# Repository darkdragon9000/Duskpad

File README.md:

## Duskpad
Duskpad is a 16-key quad-layer macro pad with an OLED display and underglow RGB using WS2812B leds running QMK and Via. it was built for Hackclub Stardance with the Hackpad misson.

## Features:
- 128x32 OLED Display
- 20 WS2812B RGB LEDs. 16 for per key lighting, and 4 layer indicators
- 16 Keys
- VIA support
  
## CAD Model:
Everything fits together using 6 M3 Bolts and heatset inserts.
It has 3 separate printed pieces. The base, the middle to clamp down on the PCB, and the top cover.

Made in onshape
## PCB
Here's my PCB! It was made in KiCad.

Schematic

## Firmware Overview
This hackpad uses [QMK](https://qmk.fm/) firmware for everything. 

- The 16 keys currently act as macros I dynamically change in VIA.
- 4 preset layers(setting,numpad, and idk what to do with the other 2)
- the top-left key runs a custom key code where, if you tap it, it sends the assigned code for that layer but if you hold it, it'll cycle to the next layer up

## BOM:
Here should be everything you need to make this hackpad

- 16x Cherry MX Switches
- 16x DSA Keycaps
- 6x M3x5x4 Heatset inserts
- 6x M3x16mm SHCS Bolts
- 16x 1N4148 DO-35 Diodes.
- 20x WS2812B LEDs
- 1x 0.91" 128x32 OLED Display
- 1x XIAO RP2040
- 1x Case (3 printed parts)

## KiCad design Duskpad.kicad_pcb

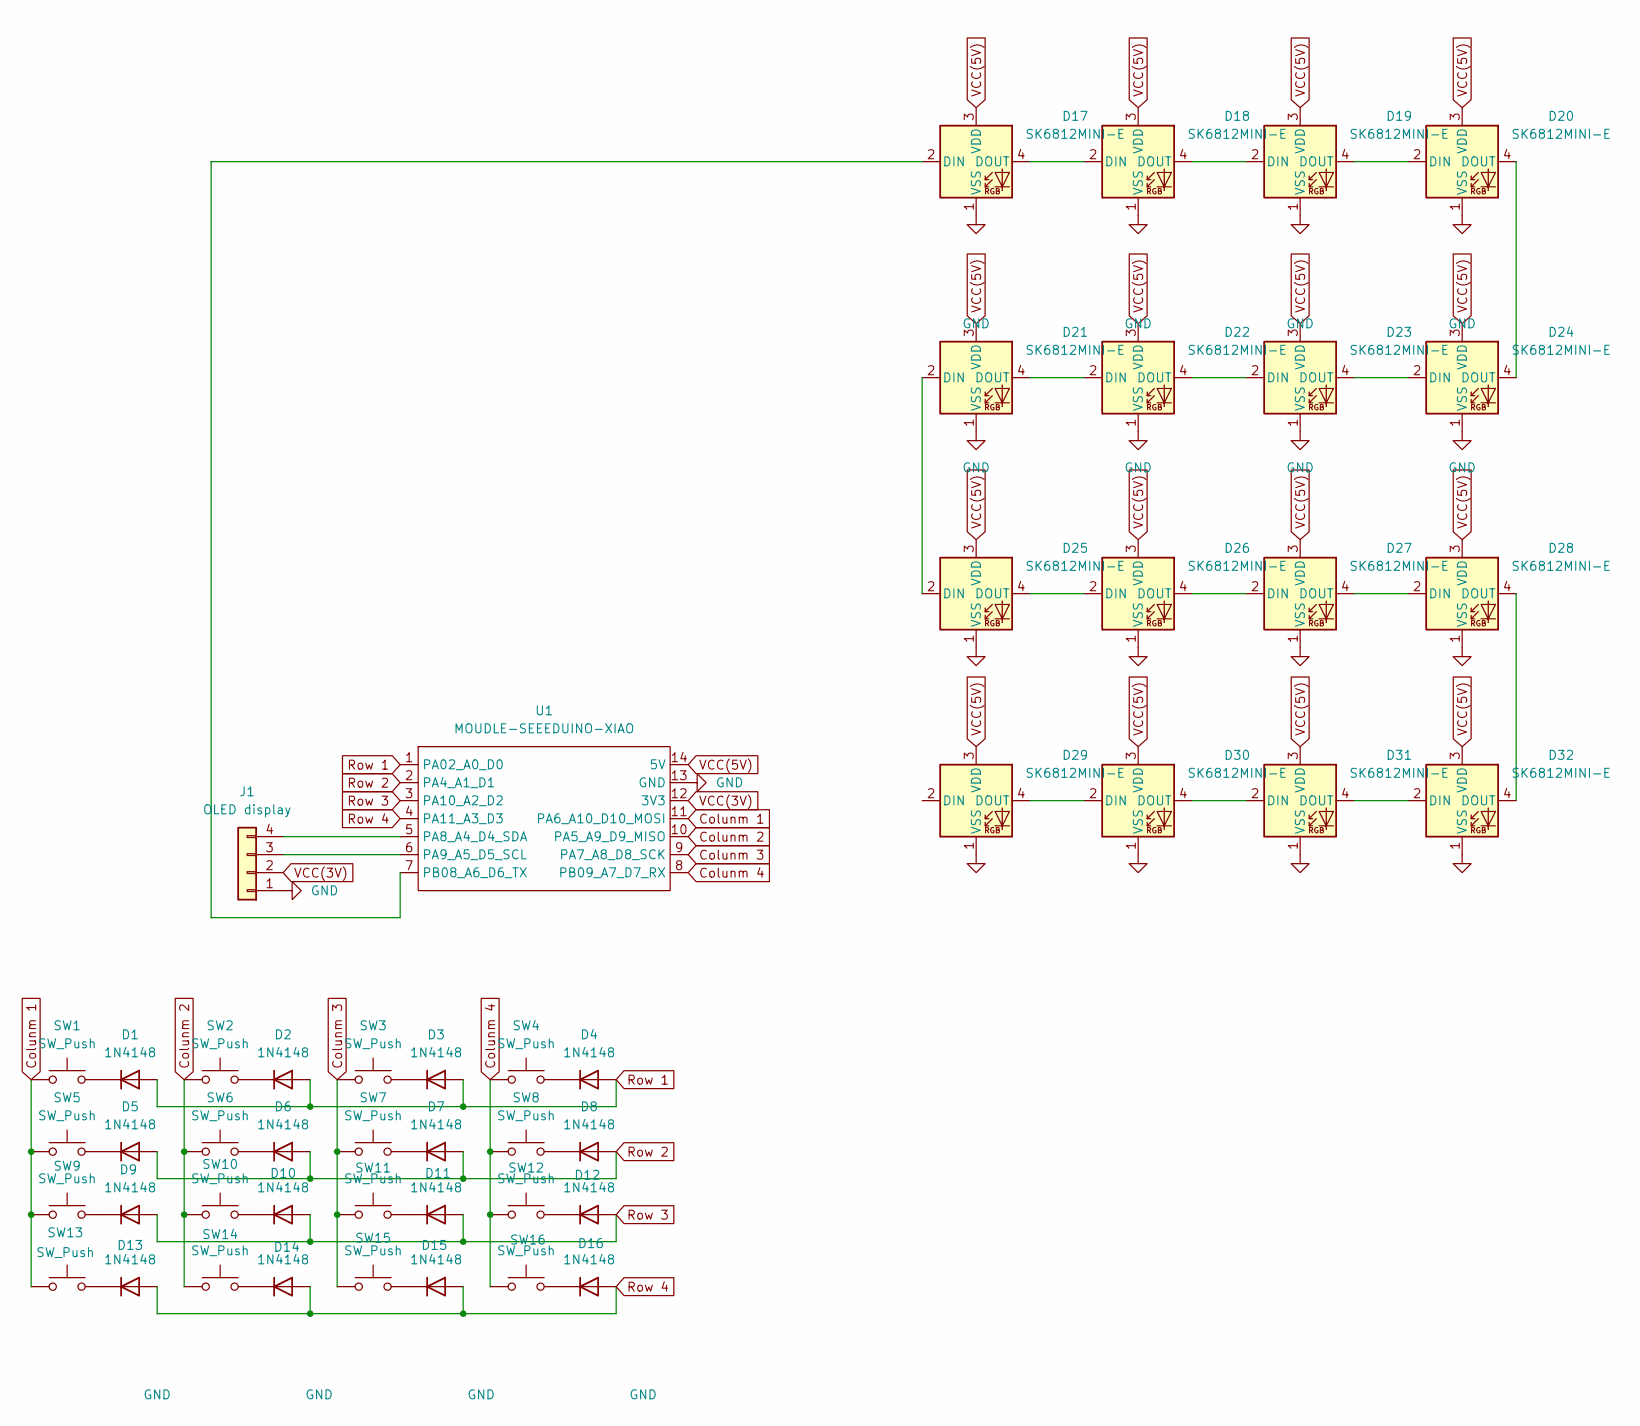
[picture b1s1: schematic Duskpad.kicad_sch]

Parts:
D1, D2, D3, D4, D5, D6, D7, D8, D9, D10, D11, D12, D13, D14, D15, D16: 1N4148; D_DO-35_SOD27_P7.62mm_Horizontal
D17, D18, D19, D20, D21, D22, D23, D24, D25, D26, D27, D28, D29, D30, D31, D32: SK6812MINI-E; LED_SK6812MINI-E_3.2x2.8mm_P1.5mm_ReverseMount
J1: OLED display; PinHeader_1x04_P2.54mm_Vertical
SW1, SW2, SW3, SW4, SW5, SW6, SW7, SW8, SW9, SW10, SW11, SW12, SW13, SW14, SW15, SW16: SW_Push; SW_Cherry_MX_1.00u_PCB
U1: MOUDLE-SEEEDUINO-XIAO; XIAO-Generic-Hybrid-14P-2.54-21X17.8MM

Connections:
Colunm 1: SW1.1, SW5.1, SW9.1, SW13.1, U1.11 (PA6_A10_D10_MOSI)
Colunm 2: SW2.1, SW6.1, SW10.1, SW14.1, U1.10 (PA5_A9_D9_MISO)
Colunm 3: SW3.1, SW7.1, SW11.1, SW15.1, U1.9 (PA7_A8_D8_SCK)
Colunm 4: SW4.1, SW8.1, SW12.1, SW16.1, U1.8 (PB09_A7_D7_RX)
DIN: D17.2 (DIN), U1.7 (PB08_A6_D6_TX)
GND: D17.1 (VSS), D18.1 (VSS), D19.1 (VSS), D20.1 (VSS), D21.1 (VSS), D22.1 (VSS), D23.1 (VSS), D24.1 (VSS), D25.1 (VSS), D26.1 (VSS), D27.1 (VSS), D28.1 (VSS), D29.1 (VSS), D30.1 (VSS), D31.1 (VSS), D32.1 (VSS), J1.1, U1.13 (GND); also elsewhere on the board
unnamed: D1.1 (K), SW1.2
unnamed: D2.1 (K), SW2.2
unnamed: D3.1 (K), SW3.2
unnamed: D4.1 (K), SW4.2
unnamed: D5.1 (K), SW5.2
unnamed: D6.1 (K), SW6.2
unnamed: D7.1 (K), SW7.2
unnamed: D8.1 (K), SW8.2
unnamed: D9.1 (K), SW9.2
unnamed: D10.1 (K), SW10.2
unnamed: D11.1 (K), SW11.2
unnamed: D12.1 (K), SW12.2
unnamed: D13.1 (K), SW13.2
unnamed: D14.1 (K), SW14.2
unnamed: D15.1 (K), SW15.2
unnamed: D16.1 (K), SW16.2
unnamed: D17.4 (DOUT), D18.2 (DIN)
unnamed: D18.4 (DOUT), D19.2 (DIN)
unnamed: D19.4 (DOUT), D20.2 (DIN)
unnamed: D20.4 (DOUT), D24.4 (DOUT)
unnamed: D21.2 (DIN), D25.2 (DIN)
unnamed: D21.4 (DOUT), D22.2 (DIN)
unnamed: D22.4 (DOUT), D23.2 (DIN)
unnamed: D23.4 (DOUT), D24.2 (DIN)
unnamed: D25.4 (DOUT), D26.2 (DIN)
unnamed: D26.4 (DOUT), D27.2 (DIN)
unnamed: D27.4 (DOUT), D28.2 (DIN)
unnamed: D28.4 (DOUT), D32.4 (DOUT)
unnamed 34: D29.2 (DIN); also elsewhere on the board
unnamed: D29.4 (DOUT), D30.2 (DIN)
unnamed: D30.4 (DOUT), D31.2 (DIN)
unnamed: D31.4 (DOUT), D32.2 (DIN)
unnamed: J1.3, U1.6 (PA9_A5_D5_SCL)
unnamed: J1.4, U1.5 (PA8_A4_D4_SDA)
Row 1: D1.2 (A), D2.2 (A), D3.2 (A), D4.2 (A), U1.1 (PA02_A0_D0)
Row 2: D5.2 (A), D6.2 (A), D7.2 (A), D8.2 (A), U1.2 (PA4_A1_D1)
Row 3: D9.2 (A), D10.2 (A), D11.2 (A), D12.2 (A), U1.3 (PA10_A2_D2)
Row 4: D13.2 (A), D14.2 (A), D15.2 (A), D16.2 (A), U1.4 (PA11_A3_D3)
VCC(3V): J1.2, U1.12 (3V3)
VCC(5V): D17.3 (VDD), D18.3 (VDD), D19.3 (VDD), D20.3 (VDD), D21.3 (VDD), D22.3 (VDD), D23.3 (VDD), D24.3 (VDD), D25.3 (VDD), D26.3 (VDD), D27.3 (VDD), D28.3 (VDD), D29.3 (VDD), D30.3 (VDD), D31.3 (VDD), D32.3 (VDD), U1.14 (5V); also elsewhere on the board

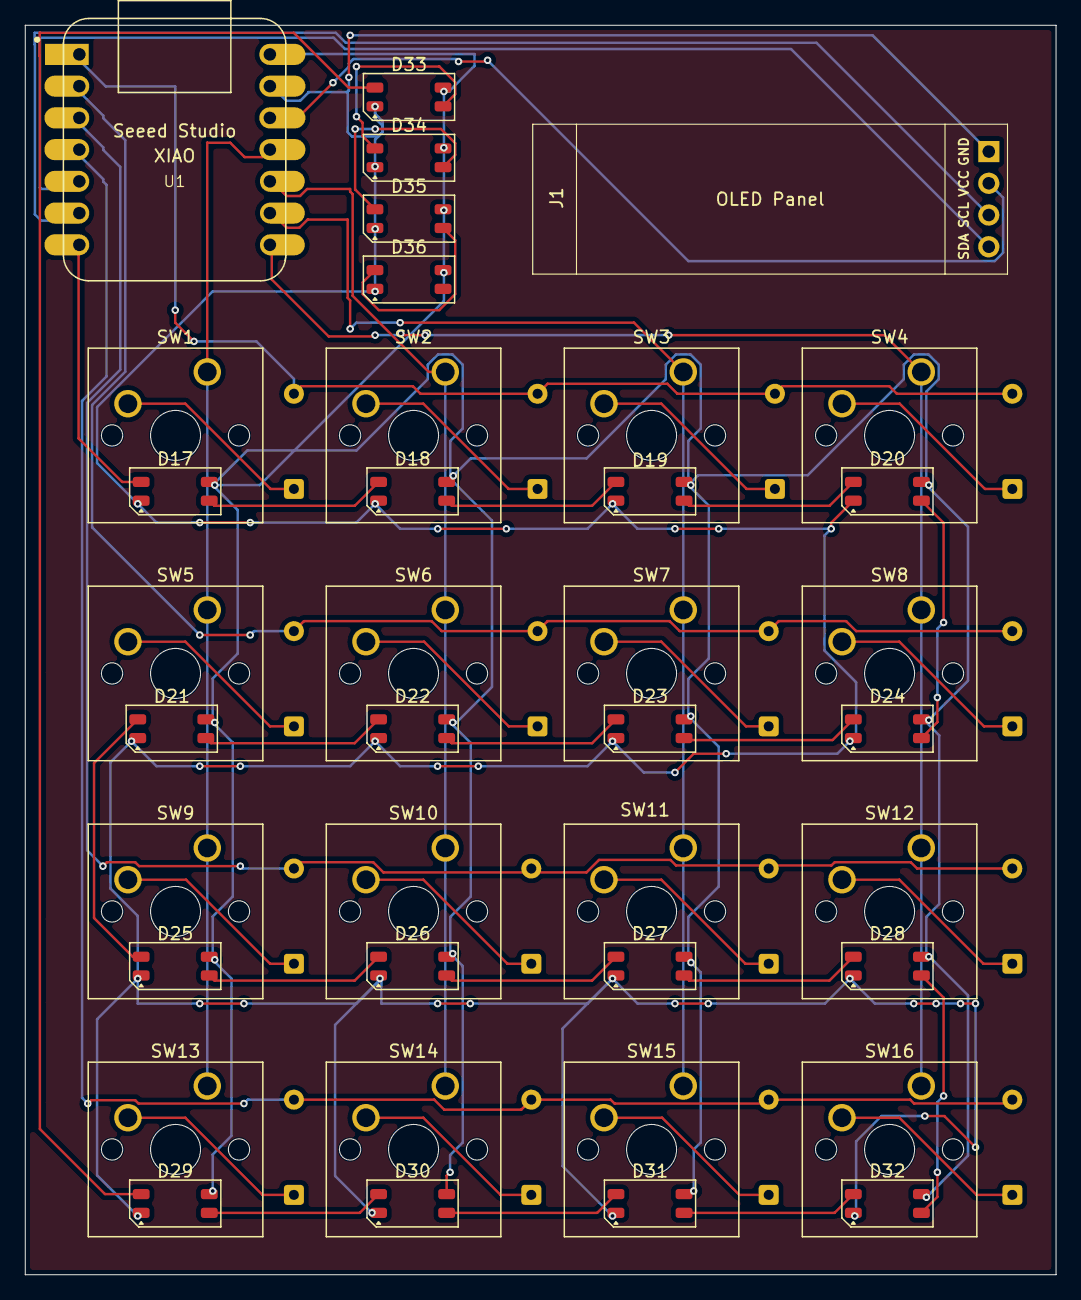
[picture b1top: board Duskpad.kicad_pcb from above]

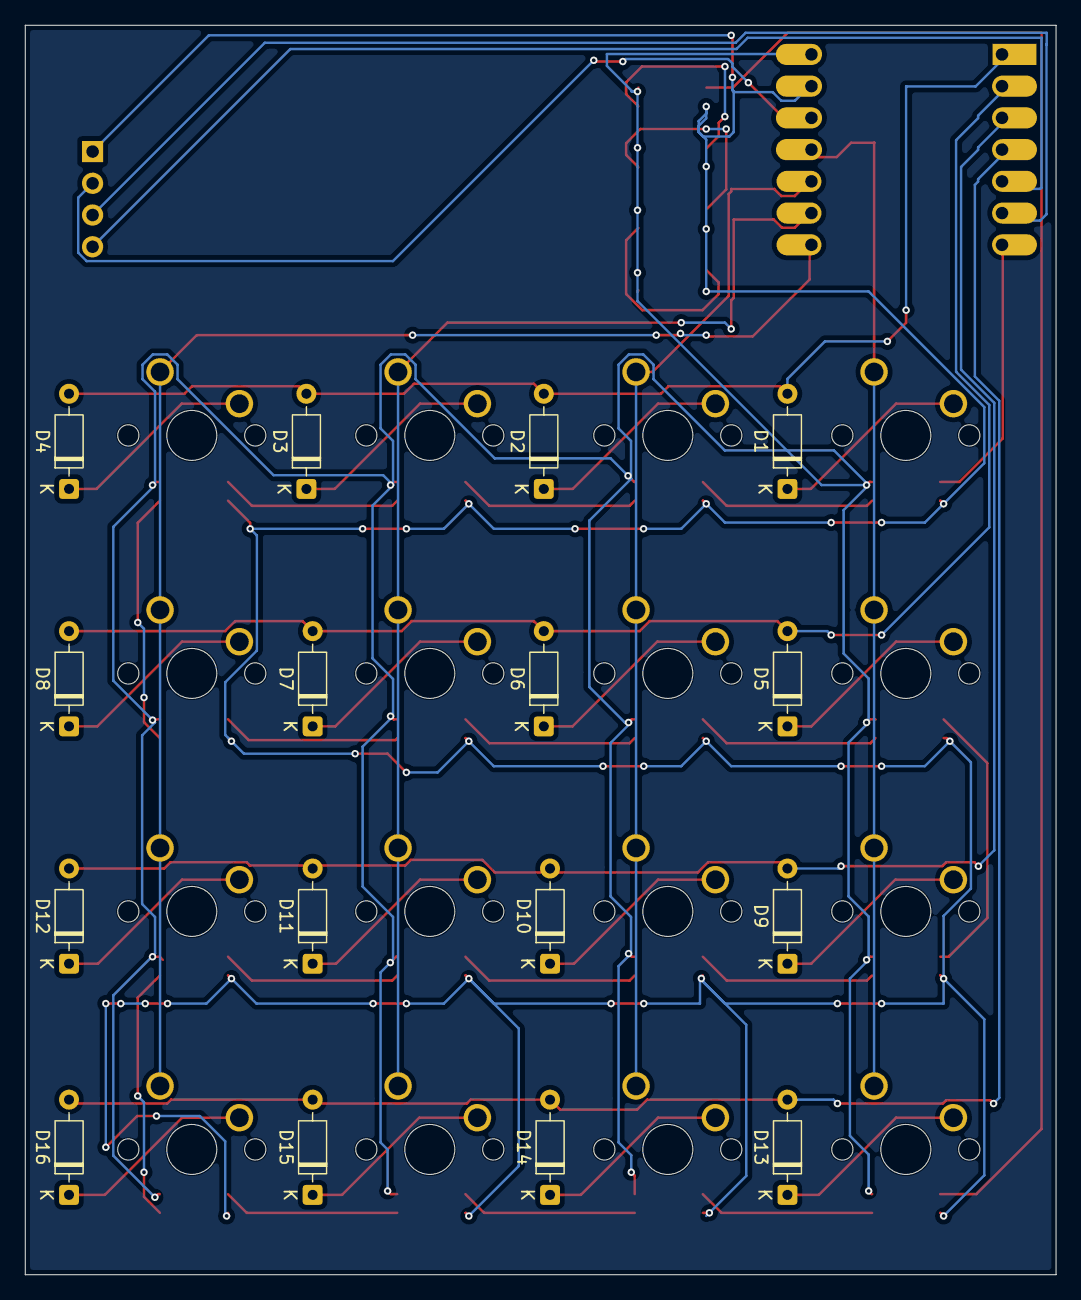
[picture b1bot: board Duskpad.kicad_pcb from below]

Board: 2 copper layers, 82.5 x 100.0 mm, 54 parts (16 on the bottom side), 49 nets.

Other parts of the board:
D33, D34, D35, D36: SK6812MINI-E; LED_SK6812MINI-E_3.2x2.8mm_P1.5mm_ReverseMount

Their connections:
GND: D33.1 (VSS), D34.1 (VSS), D35.1 (VSS), D36.1 (VSS); also elsewhere on the board
unnamed 34: D33.2 (DIN); also elsewhere on the board
unnamed: D33.4 (DOUT), D34.2 (DIN)
unnamed: D34.4 (DOUT), D35.2 (DIN)
unnamed: D35.4 (DOUT), D36.2 (DIN)
VCC(5V): D33.3 (VDD), D34.3 (VDD), D35.3 (VDD), D36.3 (VDD); also elsewhere on the board

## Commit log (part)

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2026-06-17 Added the current progress to repo
2026-06-29 did the pcb design
